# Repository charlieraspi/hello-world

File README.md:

# hello-world
charlie first git repos

today is the new day that the Lord had made we will be rejoice and glad in it!

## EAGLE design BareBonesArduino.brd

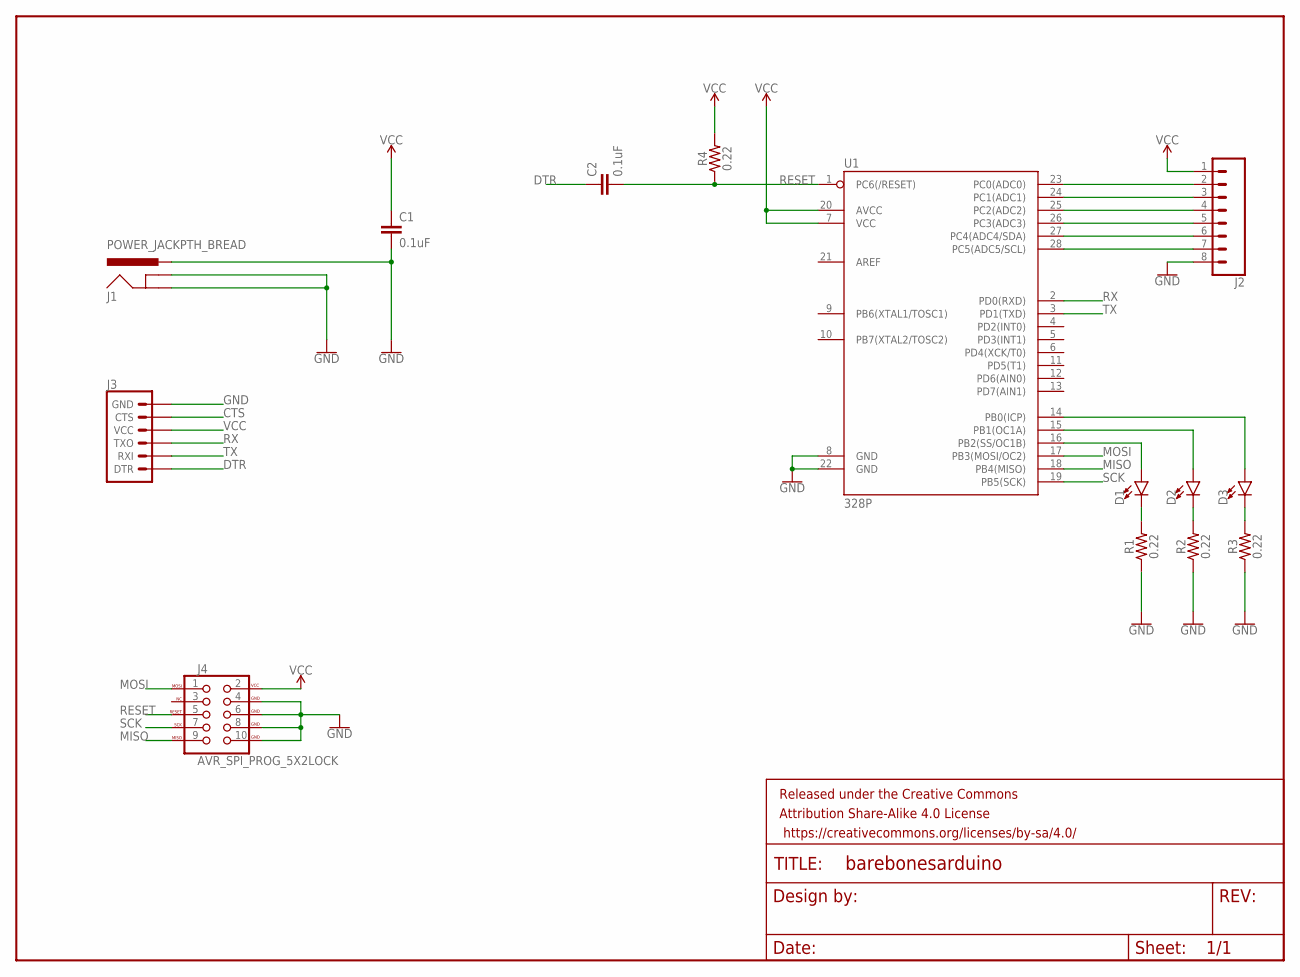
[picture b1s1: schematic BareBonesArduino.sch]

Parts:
C1, C2: 0.1uF; 0402
D1, D2, D3: LED5MM; LED_5MM
FRAME1: FRAME-LETTER; CREATIVE_COMMONS
J1: POWER_JACKPTH_BREAD; POWER_JACK_PTH_BREAD
J2: CONN_08"; 1X08
J3: 6_PIN_SERIAL_TARGETSILK; 6_PIN_SERIAL_TARGET_SIDE_W_SILK
J4: AVR_SPI_PROG_5X2LOCK; 2X5-SHROUDED_LOCK
R1, R2, R3, R4: 0.22; 0805
U1: 328P; DIP28

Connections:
CTS: J3.P$5 (CTS)
DTR: C2.1, J3.P$1 (DTR)
GND: C1.2, J1.GND, J1.GNDBREAK, J1.PWR, J2.8, J3.P$6 (GND), J4.4 (GND), J4.6 (GND), J4.8 (GND), J4.10 (GND), R1.1, R2.1, R3.1, U1.8 (GND), U1.22 (GND)
MISO: J4.9 (MISO), U1.18 (PB4(MISO))
MOSI: J4.1 (MOSI), U1.17 (PB3(MOSI/OC2))
unnamed: J2.2, U1.23 (PC0(ADC0))
unnamed: J2.3, U1.24 (PC1(ADC1))
unnamed: J2.4, U1.25 (PC2(ADC2))
unnamed: J2.5, U1.26 (PC3(ADC3))
unnamed: J2.6, U1.27 (PC4(ADC4/SDA))
unnamed: J2.7, U1.28 (PC5(ADC5/SCL))
unnamed: D3.K (C), R3.2
unnamed: D2.K (C), R2.2
unnamed: D1.K (C), R1.2
unnamed: D3.A, U1.14 (PB0(ICP))
unnamed: D2.A, U1.15 (PB1(OC1A))
unnamed: D1.A, U1.16 (PB2(SS/OC1B))
RESET: C2.2, J4.5 (RESET), R4.1, U1.1 (PC6(/RESET))
RX: J3.P$2 (TXO), U1.2 (PD0(RXD))
SCK: J4.7 (SCK), U1.19 (PB5(SCK))
TX: J3.P$3 (RXI), U1.3 (PD1(TXD))
VCC: C1.1, J2.1, J3.P$4 (VCC), J4.2 (VCC), R4.2, U1.7 (VCC), U1.20 (AVCC)

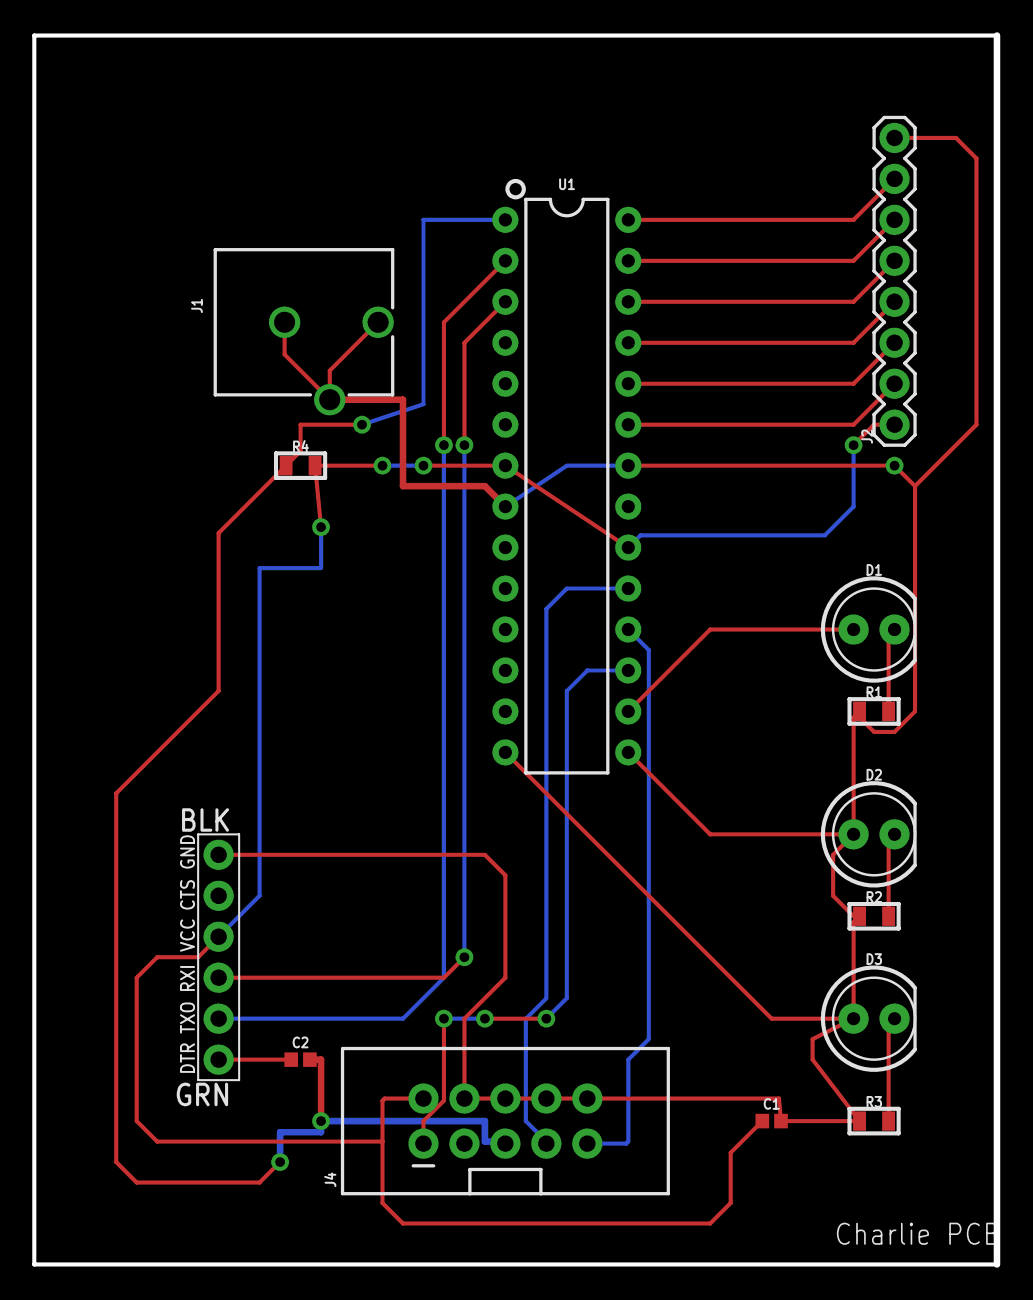
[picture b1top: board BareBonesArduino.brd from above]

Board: 2 copper layers, 59.6 x 76.2 mm, 15 parts (0 on the bottom side), 21 nets.

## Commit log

2018-01-17 finish Readme
    another day of blessing
2018-01-18 schematic change
    change in 2nd line

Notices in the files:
parts and their libraries:
SparkFun-Capacitors: Licensing: Creative Commons ShareAlike 4.0 International - https://creativecommons.org/licenses/by-sa/4.0
SparkFun-Aesthetics: Released under the Creative Commons Attribution Share-Alike 4.0 License
SparkFun-Aesthetics: https://creativecommons.org/licenses/by-sa/4.0
